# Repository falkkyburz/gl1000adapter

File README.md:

# Vector GL1000 Adapter

This is an adapter for the Vector GL1000 series of data loggers to adapt the D-SUB 25 connector to two 
D-SUB 9 standard CAN pinout connectors.

## BOM

I also included the interactive html BOM (gl1000adapter.html) 

| References     | Value                     | Footprint | Quantity |
|----------------|---------------------------|-----------|----------|
| R1             | 5k1                       | 1206      | 1        |
| R2, R3         | 120                       | 1206      | 2        |
| D1             | green                     | LED_3mm   | 1        |
| D2             | SM400                     | SOD-123   | 1        |
| SW1, SW2, SW3  | K3-2235D-K1 or similar    |           | 3        |
| J1             | DC005-T20 or similar      | 5.5/2.1mm | 1        |
| J3             | DB25 female               |           | 1        |
| J2, J4         | DB9 female                |           | 2        |
| J5, J6         | DB9 male vertical         |           | 2        |

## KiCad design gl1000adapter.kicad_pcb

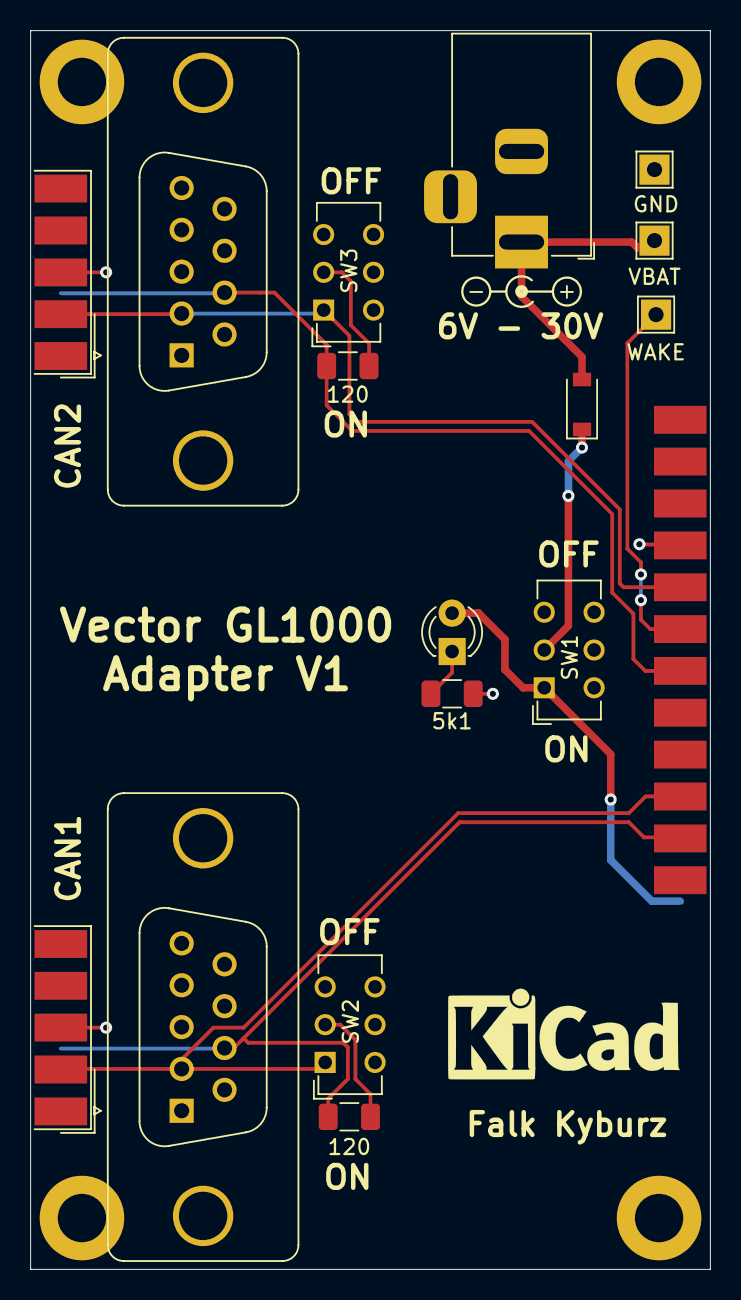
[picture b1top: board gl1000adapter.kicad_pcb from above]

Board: 2 copper layers, 45.0 x 82.0 mm, 17 parts (1 on the bottom side), 12 nets.

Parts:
D1: LED 3mm green; LED_D3.0mm
D2: SM4007PL; D_SOD-123
J1: Barrel_Jack; BarrelJack_Horizontal
J2, J4: DS1033-09FUNSiSS; DSUB-9_Female_EdgeMount_P2.77mm
J3: DB25_Female; DSUB-25_Female_EdgeMount_P2.77mm
J5, J6: DS1034-09MUNSi44; DSUB-9_Male_Vertical_P2.77x2.84mm_MountingHoles
R1: 5k1; R_1206_3216Metric
R2, R3: 120; R_1206_3216Metric
SW1, SW2, SW3: K3-2235D-K1; SW_CuK_JS202011CQN_DPDT_Straight
TP1: WAKE; TestPoint_THTPad_2.0x2.0mm_Drill1.0mm
TP12: VBAT; TestPoint_THTPad_2.0x2.0mm_Drill1.0mm
TP13: GND; TestPoint_THTPad_2.0x2.0mm_Drill1.0mm

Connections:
/CAN1H: J2.7, J3.15, J5.7, R2.1
/CAN1L: J2.2, J3.16, J5.2, SW2.1
/CAN2H: J3.19, J4.7, J6.7, R3.1
/CAN2L: J3.21, J4.2, J6.2, SW3.1
/GND: J1.2, J2.3, J2.6, J3.4, J3.7, J3.22, J4.3, J4.6, J5.3, J5.6, J6.3, J6.6, R1.2, TP13.1
/VBAT: D2.2, J1.1, TP12.1
/VBAT1: D2.1, SW1.2
/VBAT2: D1.2, J3.1, SW1.1
/WAKE: J3.20, TP1.1
unnamed: D1.1, R1.1
unnamed: R2.2, SW2.2
unnamed: R3.2, SW3.2

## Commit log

2021-05-13 Added missing value for R1.
2021-06-14 Mayor modifications, added second pair of DB9s, added switchable termination resistors.
2022-05-22 Data as ordered.
